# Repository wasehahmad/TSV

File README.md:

# TSV
Tractive System Voltage

This repository contains hardware and software for the PacMan (Pack Manager) and the AMS (Accumulator Management System)

Backup_pacman_software contains the software from the end of the 2016 project.

stable_software_20170413 contains the software on the packs at the end of the spring 2017 semester.

New_Pacman_Software contians the most recently tested software, with improvements added on to the stable_software.
Improvements include updated configuration parameters menus, power saving mode, and a lock mode that disables configutation
parameters to be edited.

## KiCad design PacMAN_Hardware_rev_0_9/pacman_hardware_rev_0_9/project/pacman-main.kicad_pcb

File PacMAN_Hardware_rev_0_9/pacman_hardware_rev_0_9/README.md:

# LFEV Pack Manager Main Board

## Overview

This directory contains the design of the LFEV "Packman" board. 
The "Packman" board, or
Pack Manager Board is responsible for 
monitoring the cells in the LFEV battery pack. This 
system contains
 a small AVR microprocessor capable of communicating high level 
data to the
SCADA system, while monitoring the pack for faults, 
managing cell charge/discharge, and tracking
the pack state of 
charge. This directory contains the PCB schematic and board 
layout
of the system.

## What's Here?

- Kicad Project
     
- Schematics
     
- Board Layouts
     
- Bill of Materials
 (OUT OF DATE --> DO NOT USE)
- Gerber Files
 
- PDF Schematic

### Directory Structure

1. `Pacman_Rev_0_8` 
-- Contains versions of the finalized board layout, send these for fabrication

2. `project` 
-- KiCad project files... Open these to change the board design

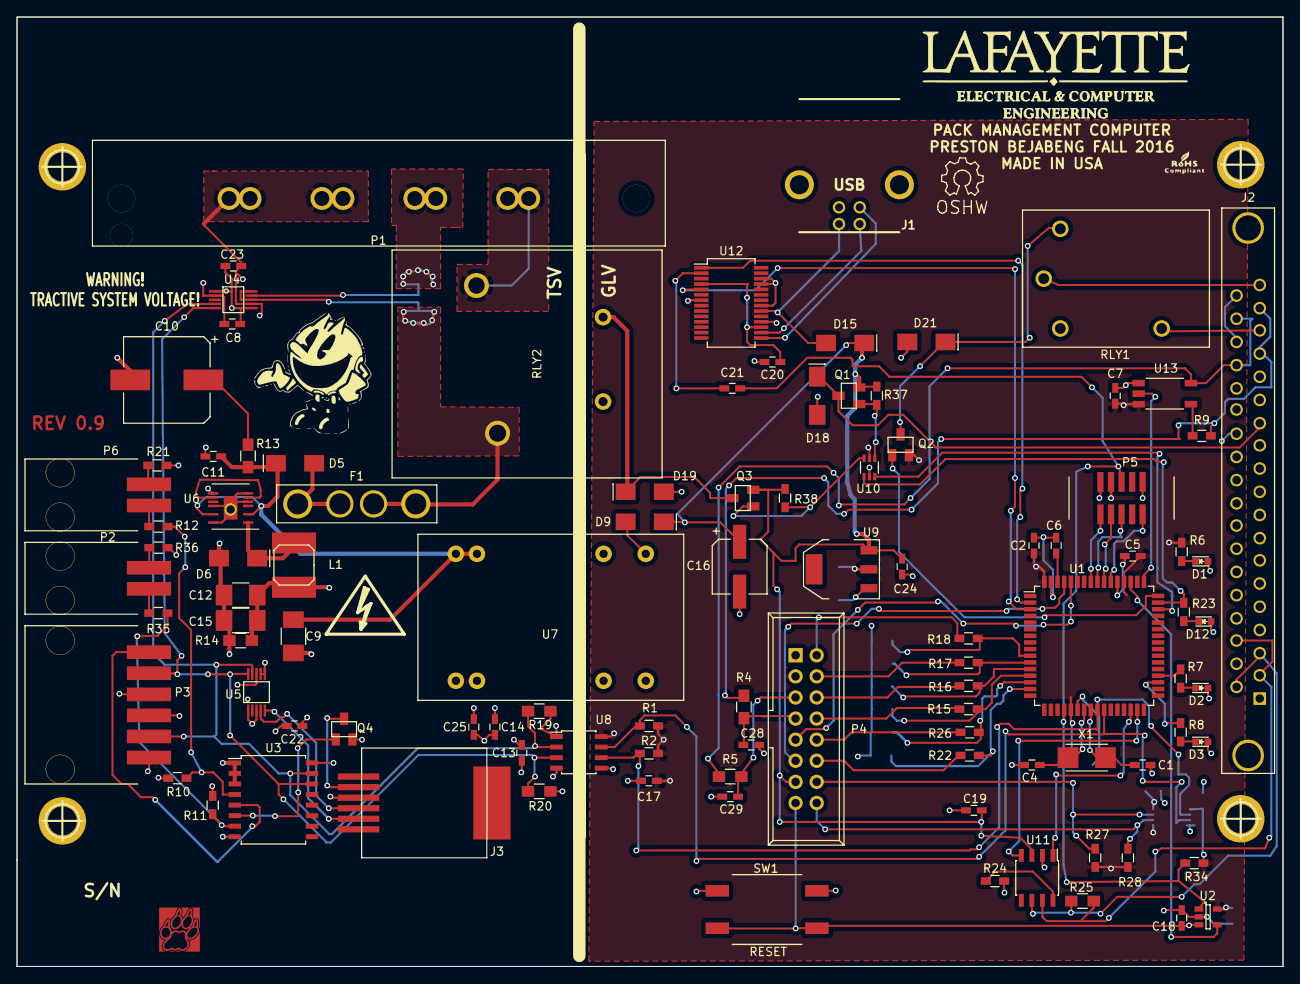
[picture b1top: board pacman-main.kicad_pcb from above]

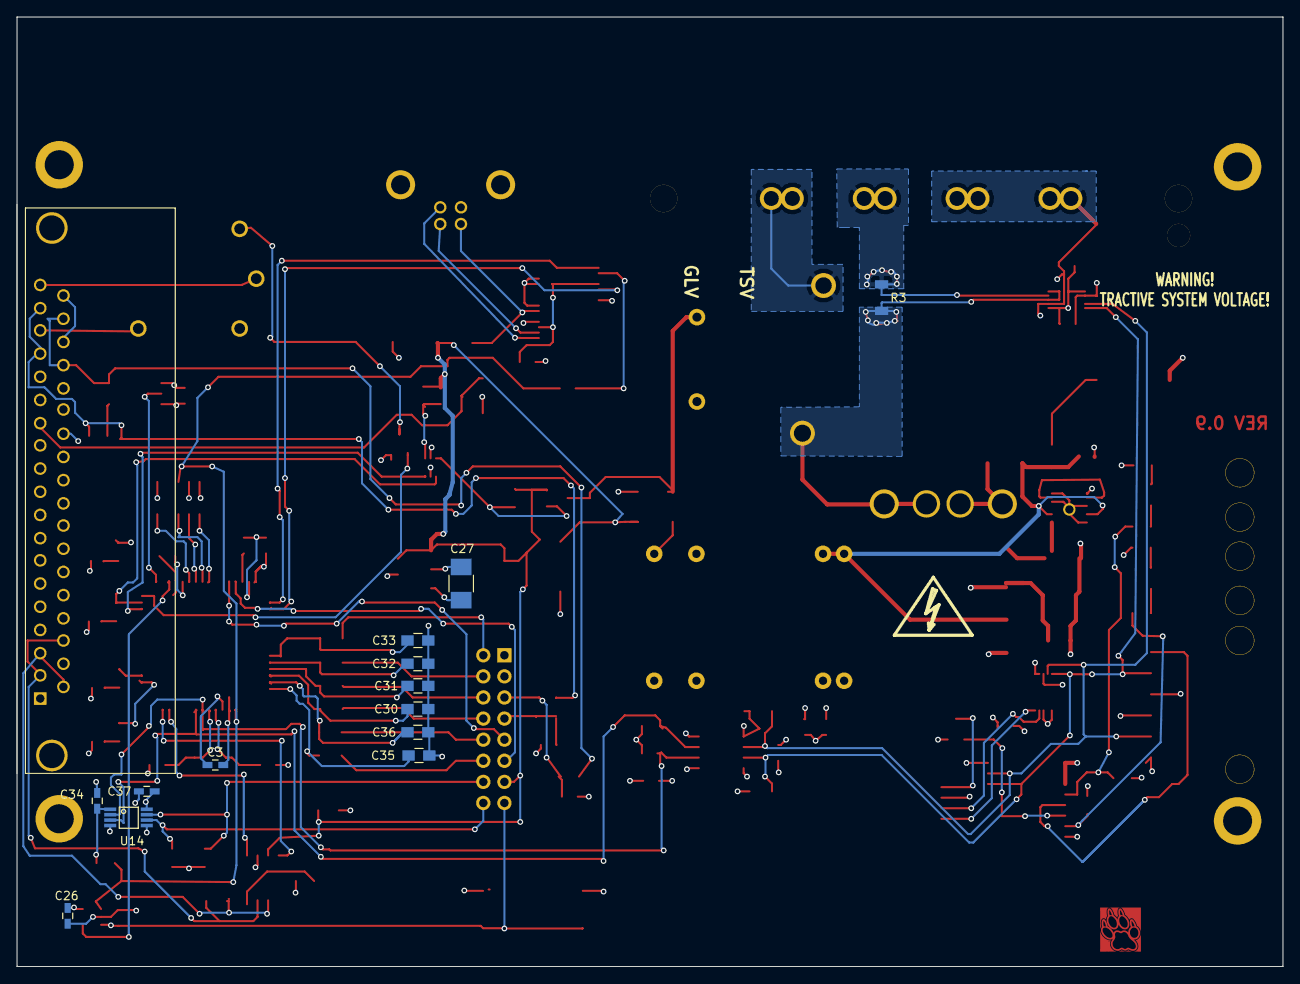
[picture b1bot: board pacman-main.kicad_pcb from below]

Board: 4 copper layers, 152.4 x 114.3 mm, 119 parts (13 on the bottom side), 90 nets.

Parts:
C1, C4: 10p; C_0603_HandSoldering
C2, C3, C5, C6, C7, C8, C13, C14, C17, C18, C19, C20, C21, C22, C23, C24, C25, C26: 0.1u; C_0603_HandSoldering
C9, C12, C15, C27: 10u; C_1210_HandSoldering
C10: 220u; c_elec_10x10
C11: 1u; C_0603_HandSoldering
C16: 220u; c_elec_6.3x7.7
C28, C29, C34, C37: .1u; C_0603_HandSoldering
C30, C31, C32, C33, C35, C36: 10u; C_0805_HandSoldering
D1: POWER; LED_0603
D2: FAULT; LED_0603
D3: SPARE; LED_0603
D5, D6, D9, D15, D18, D19, D21: SK310A-LTP; do214ac
D12: CHARGE; LED_0603
F1: 5 A; blade_fuse_holder
J1: USB; conn_usb_B
J2: BACKPLANE CONNECTOR; DB37FD
J3: RJ12; MOLEX_RJ11
L1: 220u; SELF-WE-TPC_M
P1: POWER; AMPCONN_4POS
P2: CDETECT; MOLEX_HEADER_2POS
P3: EXT I2C; MOLEX_HEADER_6POS
P4: GPIO; IDC_Header_Straight_16pins
P5: JTAG
P6: LDETECT; MOLEX_HEADER_2POS
Q1, Q2, Q3, Q4: RRR015P03TL; sot346
R1, R2, R9, R10, R11, R27, R28, R34, R37, R38: 10k; R_0603_HandSoldering
R3: 0.001 1%; CSNL1206
R4, R5: 510; R_0805_HandSoldering
R6, R7, R8, R23, R24: 1k; R_0603_HandSoldering
R12, R21, R35, R36: 100; R_0603_HandSoldering
R13: 1 1%; R_0805_HandSoldering
R14, R19, R20: 1k; R_0805_HandSoldering
R15, R16, R17, R18, R22, R26: 510; R_0603_HandSoldering
R25: 120; R_0805_HandSoldering
RLY1: G5LE-1A4 DC3; relay_G5LE_1A4
RLY2: T9AS1D12-5; RLY_T9AS1D12-5
SW1: RESET; SW_RACON_8
U1: AT90CAN128-M; TQFP-64_14x14mm_Pitch0.8mm
U2: ADM6320; SOT-23-5
U3: PCF8574A; SOIC-16_7.5x10.3mm_Pitch1.27mm
U4: INA_226; msop_10_ads1015
U5: ADS1115; msop_10_ads1015
U6: LTC3638; TSSOP16_LTC3638
U7: NCS6S1205C
U8: Si8600; SOIC-8_3.9x4.9mm_Pitch1.27mm
U9: NCP1117ST33T3G; SOT-223
U10: SN74LVC2G06; DCK
U11: MCP2551-I/SN; SOIC-8_3.9x4.9mm_Pitch1.27mm
U12: FT232RL; SSOP-28_5.3x10.2mm_Pitch0.65mm
U13: TLP2361
U14: TCA9617B
VAL: REF; lafLogo
X1: 10MHz; crystal_TXC_7A
hole_3mm5, hole_3mm5#2, hole_3mm5#3, hole_3mm5#4: VAL**; hole_3mm5

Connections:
5V_AMPS: J3.5, Q4.3
5V_HV: C8.1, C12.1, C13.1, C14.1, C15.1, C22.1, C23.1, C25.1, L1.2, P3.3, Q4.2, R10.1, R11.2, R14.2, R19.2, R20.2, U3.16, U4.1, U4.6, U5.8, U6.9, U8.1
+3V3: C2.1, C3.1, C5.1, C7.1, C17.1, C26.1, C27.1, C34.1, C37.1, P4.3, P5.4, Q2.2, R1.1, R2.1, R6.2, R27.1, R28.1, R34.1, U1.21, U1.52, U1.64, U2.5, U8.8, U9.2, U10.5, U13.6, U14.1, U14.5, U14.8
+5V: C16.1, C19.1, C24.1, D9.2, D15.2, P4.13, Q1.2, Q3.2, R37.2, R38.2, U9.3, U11.3
/CAN Transceiver/CANRX: U1.31, U11.4
/CAN Transceiver/CANTX: U1.30, U11.1
/External Connectors/PB0: C33.1, R18.1, U1.10
/External Connectors/PB1: C32.1, R17.1, U1.11
/External Connectors/PB2: C31.1, R16.1, U1.12
/External Connectors/PB3: C30.1, R15.1, U1.13
/External Connectors/PB4: C36.1, R26.1, U1.14
/External Connectors/PB5: C35.1, R22.1, U1.15
/External Connectors/PIN2: P4.2, R18.2
/External Connectors/PIN4: P4.4, R17.2
/External Connectors/PIN6: P4.6, R16.2
/External Connectors/PIN8: P4.8, R15.2
/External Connectors/PIN10: P4.10, R26.2
/External Connectors/PIN12: P4.12, R22.2
/External Connectors/SCL_IN: P4.14, R27.2, U14.7
/External Connectors/SDA_IN: P4.16, R28.2, U14.6
/External Connectors/SLOOP_A2: J2.35, J2.37
/FTDI USB UART/DTR: C21.1, U12.2
/FTDI USB UART/RXD: U1.3, U12.5
/FTDI USB UART/TXD: U1.2, U12.1
/Isolated Power Supply/HV_PWR: C9.1, C11.1, D5.2, R13.1, U6.3, U6.14, U7.22, U7.23
/PC0: R8.2, U1.35
/PC1: R7.2, U1.36
/Safety Loop Wiring/CHARGE_CTRL: R23.2, U1.47, U10.1
/Safety Loop Wiring/FAN_CTRL: U1.46, U10.3
/Safety Loop Wiring/SAFETY_CTRL: Q2.1, U1.48
/Safety Loop Wiring/~CHRG_CTRL: Q3.1, R38.1, U10.6
/Safety Loop Wiring/~FAN_CTRL: Q1.1, R37.1, U10.4
/WATCHDOG: U1.51, U2.4
ADC0: P4.11, U1.61
ADC1: P4.9, U1.60
AMS_RESET: P3.6, U3.5
BATT+: P1.3, R3.2, U4.9
CANH: J2.2, J2.22, R25.1, U11.7
CANL: J2.3, J2.20, R25.2, U11.6
CHARGE+: P1.4, RLY2.1
CURRENT_HV_1: J3.3, U5.4
CURRENT_HV_2: J3.2, U5.5
FAN+: D18.2, J2.13, Q1.3
GND: C1.2, C2.2, C3.2, C4.2, C5.2, C6.2, C7.2, C16.2, C17.2, C18.2, C19.2, C20.2, C24.2, C26.2, C27.2, C28.2, C29.2, C30.2, C31.2, C32.2, C33.2, C34.2, C35.2, C36.2, C37.2, D1.2, D2.2, D3.2, D12.2, D18.1, D19.1, D21.1, J1.4, J1.5, J1.6, J2.31, P4.1, P5.2, P5.10, R24.2, RLY1.2, RLY2.2, SW1.2, U1.22, U1.53, U1.63, U2.2, U7.16, U8.5, U9.1, U10.2, U11.2, U12.7, U12.18, U12.21, U12.25, U12.26, U13.4, U14.4
LED+: C28.1, P4.7, R4.1
LED-: C29.1, P4.5, R5.2
unnamed: C1.1, U1.24, X1.1
unnamed: C4.1, U1.23, X1.2
unnamed: C6.1, U1.62
unnamed: C10.1, R13.2
unnamed: C20.1, U12.4, U12.17
unnamed: D1.1, R6.1
unnamed: D2.1, R7.1
unnamed: D3.1, R8.1
unnamed: D5.1, F1.2
unnamed: D6.2, L1.1, U6.1
unnamed: D9.1, U7.14
unnamed: D12.1, R23.1
unnamed: D19.2, Q3.3, RLY2.5
unnamed: D21.2, Q2.3, RLY1.5
unnamed: P2.1, R35.2
unnamed: P2.2, R36.2
unnamed: P6.1, R12.2
unnamed: P6.2, R21.2
unnamed: Q4.1, U3.6
unnamed: R9.1, U13.1
unnamed: R24.1, U11.8
unnamed: U6.7, U6.10
PACK+: F1.1, R3.1, RLY2.3, U4.8, U4.10
PACK-: C8.2, C9.2, C10.2, C11.2, C12.2, C13.2, C14.2, C15.2, C22.2, C23.2, C25.2, D6.1, J3.4, P1.1, P1.2, P3.1, P3.4, R14.1, R21.1, R36.1, U3.1, U3.2, U3.3, U3.8, U4.2, U4.7, U5.1, U5.3, U5.6, U5.7, U6.6, U6.8, U6.12, U6.16, U6.17, U7.2, U7.3, U8.4
SCL_HV: P3.5, R20.1, U3.14, U4.5, U5.10, U8.3
SDA_HV: P3.2, R19.1, U3.15, U4.4, U5.9, U8.2
SLOOP_A1: J2.19, RLY1.1
SLOOP_A3: J2.16, J2.18, R4.2, R9.2
SLOOP_A4: J2.34, J2.36, R5.1, U13.3
SLOOP_B1: J2.17, RLY1.3
SLOOP_DET: U1.49, U13.5
SW_SCL: R2.2, U1.25, U8.6, U14.2
SW_SDA: R1.2, U1.26, U8.7, U14.3
TCK: P5.1, U1.57
TDI: P5.9, U1.54
TDO: P5.3, U1.55
TMS: P5.5, U1.56
USBD+: J1.3, U12.15
USBD-: J1.2, U12.16
VUSB: D15.1, J1.1, U12.20
~CHRG_DET: R10.2, R12.1, U3.4
~LOW_DET: R11.1, R35.1, U3.7
~RESET: C18.1, P4.15, SW1.1, U2.3
~RESET_AVR: C21.2, P5.6, R34.2, U1.20, U2.1

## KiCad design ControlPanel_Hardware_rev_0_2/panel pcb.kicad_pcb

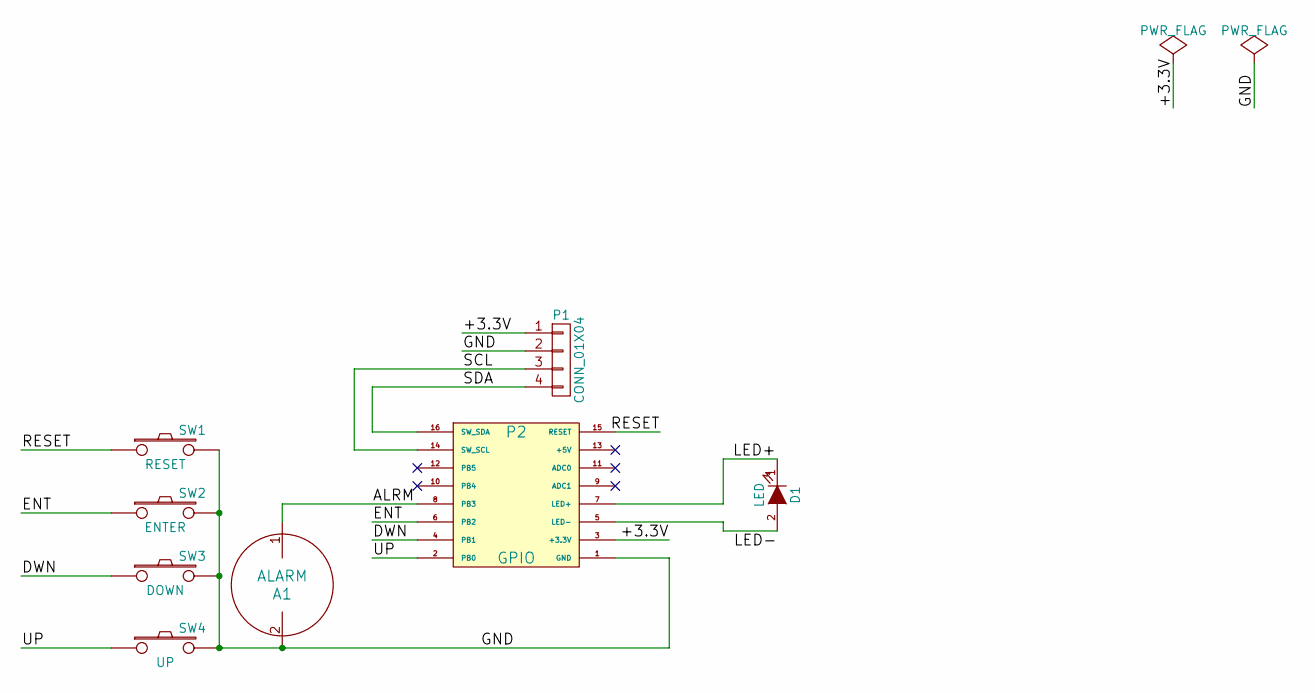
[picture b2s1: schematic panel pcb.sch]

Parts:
A1: ALARM; Manufacturer PN AI-1027-TWT-5V-2-R
D1: LED; LED_D5.0mm; Manufacturer P/N WP56BSRD/B
P1: CONN_01X04; MOLEX4Vert
P2: GPIO; IDC_Header_Straight_16pins
SW1: RESET; SW_RACON_8; Manufacturer PN 1.14100.5030000
SW2: ENTER; SW_RACON_8; Manufacturer PN 1.14100.5030000
SW3: DOWN; SW_RACON_8; Manufacturer PN 1.14100.5030000
SW4: UP; SW_RACON_8; Manufacturer PN 1.14100.5030000

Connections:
/+3.3V: P1.1, P2.3 (+3.3V)
/ALRM: A1.1, P2.8 (PB3)
/DWN: P2.4 (PB1), SW3.1
/ENT: P2.6 (PB2), SW2.1
/GND: A1.2, P1.2, P2.1 (GND), SW1.2, SW2.2, SW3.2, SW4.2
/LED+: D1.1 (K), P2.7 (LED+)
/RESET: P2.15 (RESET), SW1.1
/SCL: P1.3, P2.14 (SW_SCL)
/SDA: P1.4, P2.16 (SW_SDA)
/UP: P2.2 (PB0), SW4.1
unnamed: D1.2 (A), P2.5 (LED-)

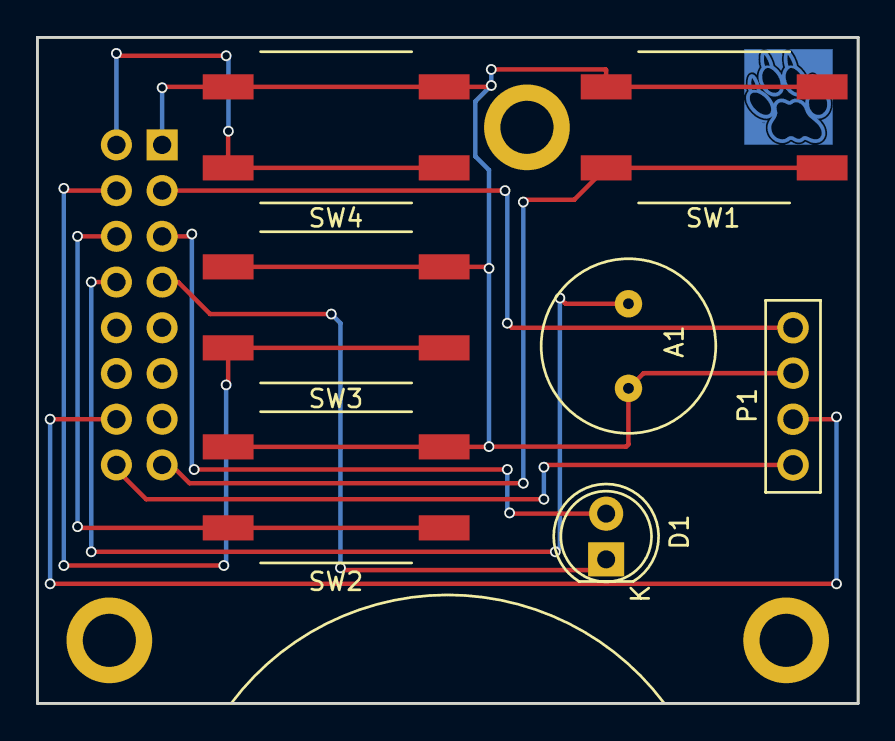
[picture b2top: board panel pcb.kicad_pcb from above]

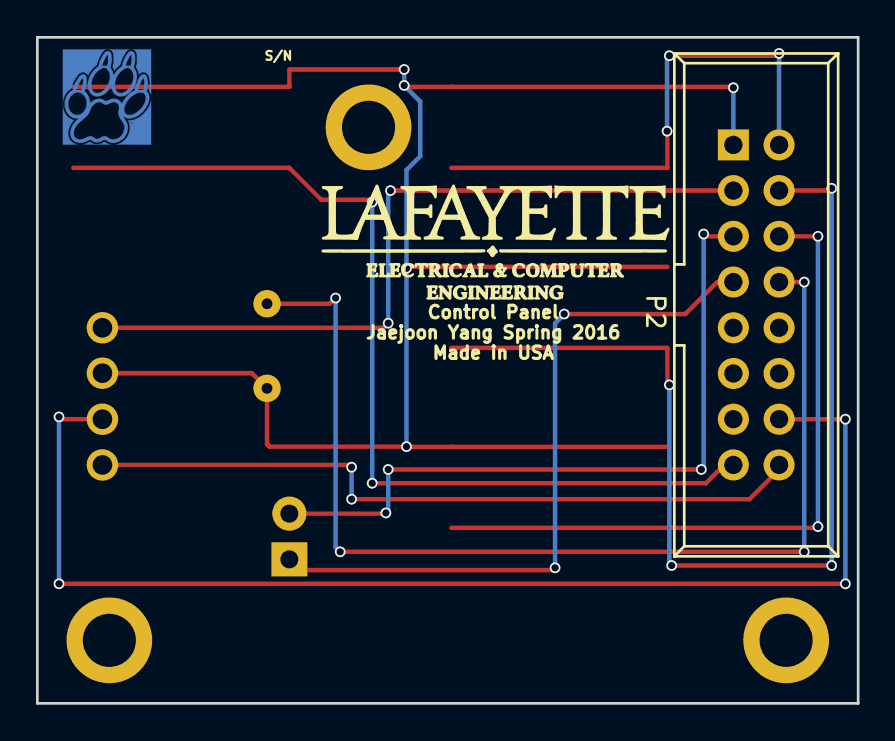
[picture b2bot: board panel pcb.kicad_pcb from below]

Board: 2 copper layers, 45.6 x 37.0 mm, 9 parts (2 on the bottom side), 11 nets.

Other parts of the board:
VAL: REF; lafLogo

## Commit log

2017-01-27 Test test
2017-01-31 Pushed rev 0.8 schematic
2017-01-31 Added in annotations about hardware changed
2017-03-10 adding new packman software to repo
2017-03-30 Add files via upload
    PacMAN Hardware Rev 0.9. Moved C3, C5. Removed D20.
2017-04-01 Began updates on pacman software. Now sends can according to new conventions. More updates to come
2017-04-02 tested can stuff, and added pack id configurability. more to debug... works for now
2017-04-02 little updates
2017-04-02 quick change
2017-04-03 FIGURED IT OUT AND FIXED THE CURRENT PROBLEMS :)
2017-04-03 Adding working backup version of the software
2017-04-04 fixed the bug in new pacman software
2017-04-05 minor updates
2017-04-06 made some updates, including configuring number of cells, fixing pack id set
2017-04-07 minor changes, working on detailed error viewing
2017-04-09 Added new schematic/PCB layout for revised Control Panel; schematic/pcb not yet reviewed by Nadovich.
2017-04-10 Added new directory to revert to in case of disaster. Also working on state transition logging. Still needs to be displayed on screen
2017-04-11 fixed (most of) the display bugs. it works
2017-04-11 fixed a few bugs
2017-04-12 logging logs most recent fault condition. also fixed the yoda-like display
2017-04-12 new fualt displays
2017-04-12 showing hex val for fault val now
2017-04-12 trying to fix the enter button
2017-04-12 fixd type
2017-04-12 fixing the thing crashing when a fault occurs and we try to view its log
2017-04-12 fixing crash bug
2017-04-13 adding i2c workaround
2017-04-13 added other workaround for soc and i2c
2017-04-13 need to see hex values on screen
2017-04-13 adding a workaround for i2c problem for temperature sensor
2017-04-13 workaround for temp and i2c
2017-04-13 fixed can buggit add .!
2017-04-13 saving off new folder with current version of stable, working software
2017-04-13 makefile now preserves eeprom. also if no buttons are pressed, lcd display goes back to main screen
2017-04-13 minor things
2017-04-17 added risky folder. contains un-tested software. current revision removes fault 3, and revises i2c daq protocol, trying to be more accurate
2017-04-24 some changes. evaluating soon, but joe's kicking me off this computer
2017-04-24 software is stable. LCD display turns off after 2 mins inactivity
2017-04-25 lcd display now turns off correctly after 2 minutes of inactivity. Seems to draw ~10mA less
2017-04-26 added a readme
2017-04-26 beginning memory management overhaul. more to come
2017-04-26 Finished (for now) memory management fixes. Cleared up around 10%
2017-04-26 adjusted pushbutton delays
2017-04-27 working on config params page
2017-05-03 configuration parameters screen works
2017-05-03 added lock state
2017-05-04 lock and config screen is fully cuntional. probably the last software edits of the year. everything in stable and working order :)
2017-05-04 Added new watchdog frequency for AMS boards.
2017-05-04 cleaned up software folders and readme.
2017-05-12 Added todos to fix known bugs
2017-05-16 Updated undervoltage logic
2017-05-16 Fix for display implemented, moved to v0.17
2018-01-24 Fixed debouncing of buttons. Adding new param for min_cell_voltage
2018-01-24 Added param for min_voltage
2018-01-24 Created a notes file
2018-01-24 Minor bug fix to param max_min cell voltage mixup
2018-01-25 Added two new params. max cell charge voltage and min current
2018-01-25 Made lock config to cause a fault is unlocked
2018-01-25 Started working on fixing the watchdog timer
2018-01-25 Added watch dog counters to each task after for loop. added reseting code to watchdog
2018-01-25 Fixed bug with for loop
2018-01-31 Changed condition for lower voltage threshold
2018-02-13 Edited
2018-02-14 Updated notes
2018-02-15 Fixed watchdog bug by taking care of overflow
2018-02-15 Fixed watchdog error. I wasnt resetting the timer
2018-02-22 Updated max cell charge voltasge from 37 to 3700
2018-02-28 Made I2C not necessary for watchdog
2018-03-05 Added time delay hardware and changed watchdog back. check notes
2018-03-07 Updated notes and watchdog delay
2018-03-11 Updated lcd to have only two screens for cell status and display config values with num
2018-03-17 Fixed errors in updated UI
2018-03-17 Fixed enter button
2018-03-20 Fixed UI display and SOC problem of dropping every time it resets
2018-03-23 Updated SOC code
2018-03-23 Change default values
2018-03-23 Changed display during charging
2018-03-24 Added new set_soc config
2018-03-30 Added new config
2018-04-05 Added new can data to send sloop status
